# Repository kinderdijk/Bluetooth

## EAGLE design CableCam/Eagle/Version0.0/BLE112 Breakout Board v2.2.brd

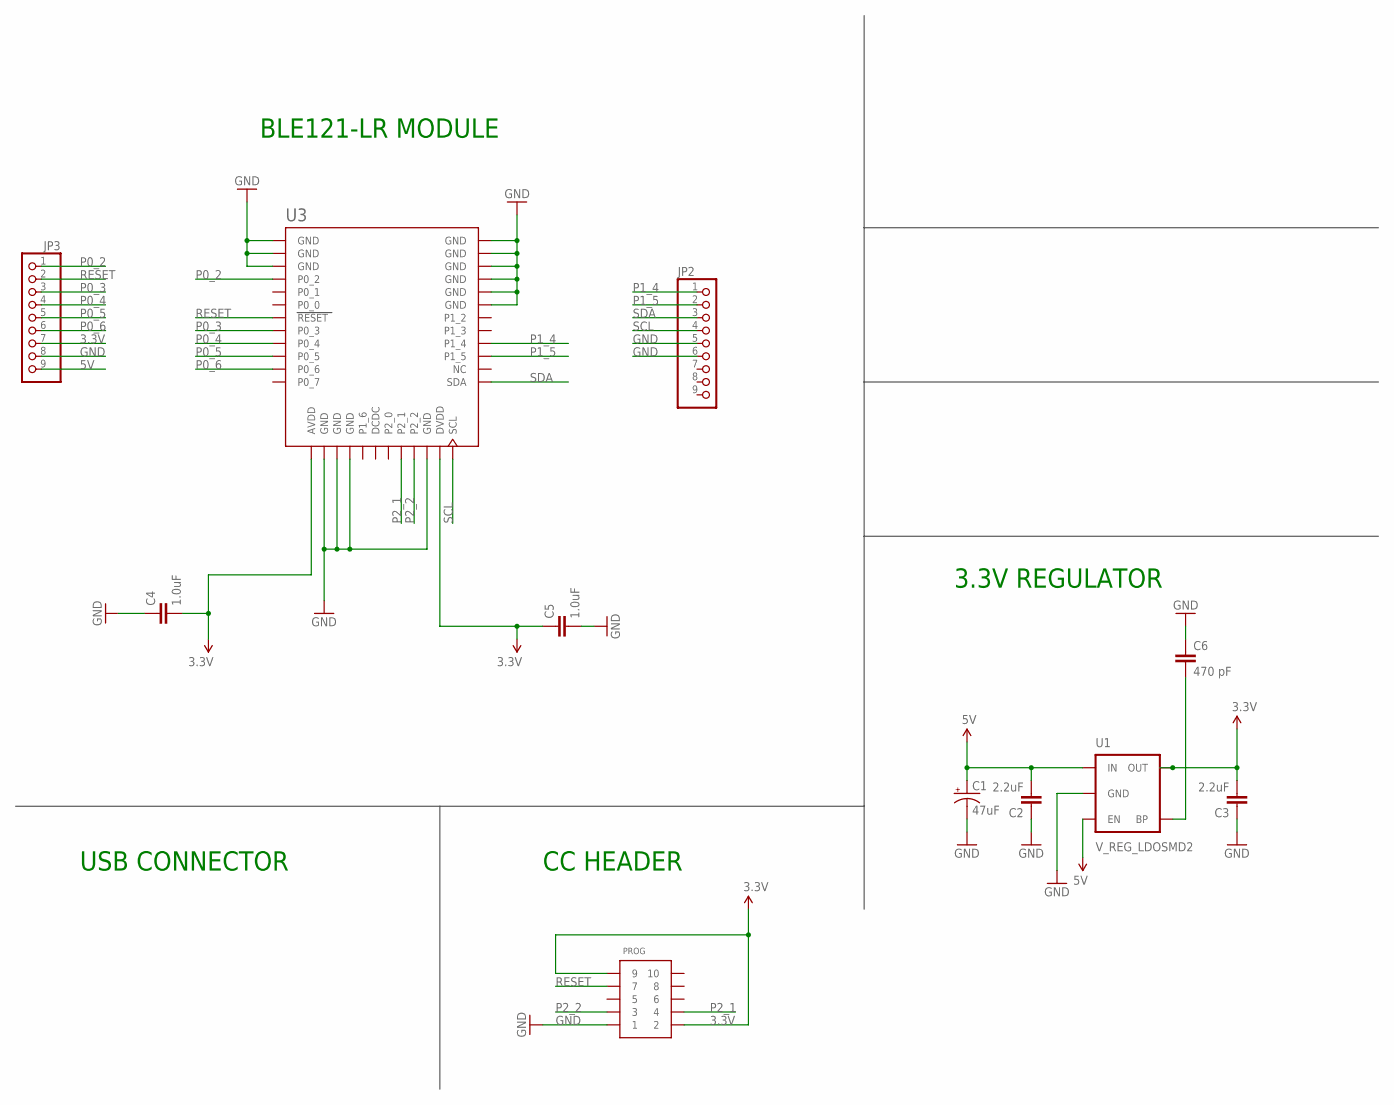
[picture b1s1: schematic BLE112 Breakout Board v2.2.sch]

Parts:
C1: 47uF; PANASONIC_D
C2, C3: 2.2uF; 0402-CAP
C4, C5: 1.0uF; 0402-CAP
C6: 470 pF; 0402-CAP
JP2, JP3: PINHD-1X9; 1X09-BIG
PROG: CONN_5-2-FTSH-V; FTSH-105-DV
U1: V_REG_LDOSMD2; SC70
U3: BLE121LR-VISUAL-A; BLE121LR-A

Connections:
3.3V: C3.2, C4.2, C5.1, JP3.7, PROG.2, PROG.9, U1.5 (OUT), U3.AVDD, U3.DVDD
5V: C1.+, C2.2, JP3.9, U1.1 (IN), U1.3 (EN)
GND: C1.-, C2.1, C3.1, C4.1, C5.2, C6.1, JP2.5, JP2.6, JP3.8, PROG.1, U1.2 (GND), U3.GND, U3.GND@2 (GND), U3.GND@3 (GND), U3.GND@4 (GND), U3.GND@5 (GND), U3.GND@6 (GND), U3.GND@7 (GND), U3.GND@8 (GND), U3.GND@9 (GND), U3.GND@10 (GND), U3.GND@11 (GND), U3.GND@12 (GND), U3.GND@13 (GND)
unnamed: C6.2, U1.4 (BP)
P0_2: JP3.1, U3.P0_2
P0_3: JP3.3, U3.P0_3
P0_4: JP3.4, U3.P0_4
P0_5: JP3.5, U3.P0_5
P0_6: JP3.6, U3.P0_6
P1_4: JP2.1, U3.P1_4
P1_5: JP2.2, U3.P1_5
P2_1: PROG.4, U3.P2_1
P2_2: PROG.3, U3.P2_2
RESET: JP3.2, PROG.7, U3.RESET
SCL: JP2.4, U3.SCL
SDA: JP2.3, U3.SDA

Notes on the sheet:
USB CONNECTOR
CC HEADER
3.3V REGULATOR
BLE121-LR MODULE

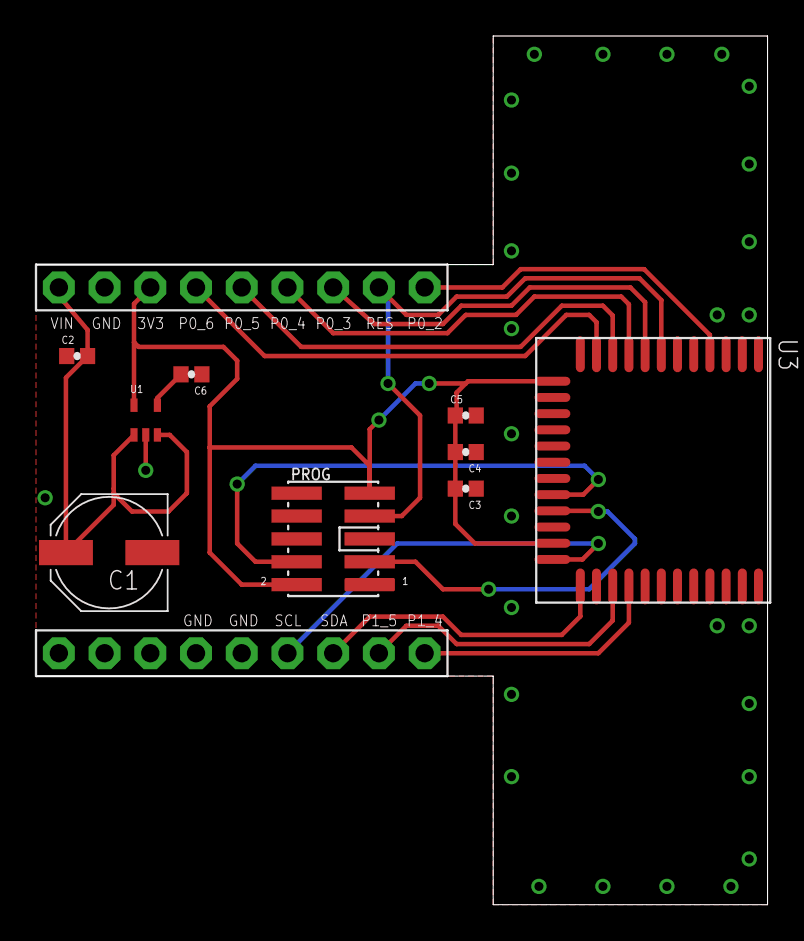
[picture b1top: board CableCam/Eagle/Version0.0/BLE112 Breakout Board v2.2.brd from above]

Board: 2 copper layers, 40.6 x 48.3 mm, 11 parts (0 on the bottom side), 16 nets.

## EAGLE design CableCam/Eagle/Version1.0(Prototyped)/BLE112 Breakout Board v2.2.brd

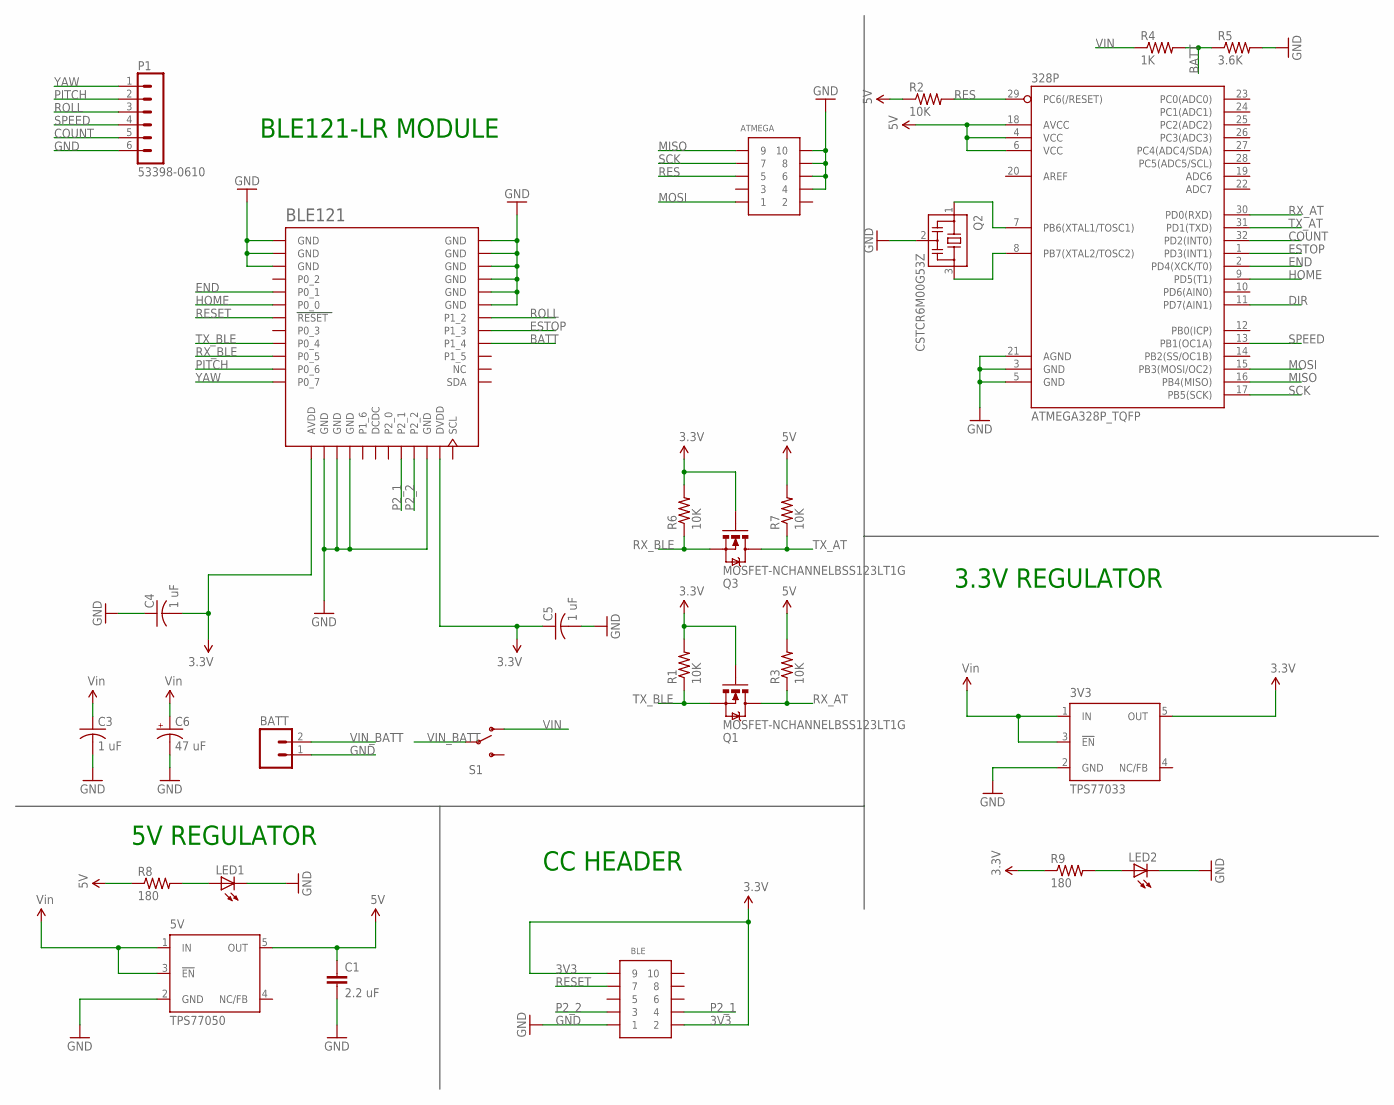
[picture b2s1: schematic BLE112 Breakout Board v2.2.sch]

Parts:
3V3: TPS77033; SOT23-DBV
5V: TPS77050; SOT23-DBV
328P: ATMEGA328P_TQFP; TQFP32-08
ATMEGA: CONN_5-2-FTSH-V; FTSH-105-DV
BATT: M02JST-PTH-2; JST-2-PTH
BLE: CONN_5-2-FTSH-V; FTSH-105-DV
BLE121: BLE121LR-VISUAL-A; BLE121LR-A
C1: 2.2 uF; 0603-CAP
C3, C4, C5: 1 uF; C0402
C6: 47 uF; PANASONIC_D
LED1, LED2: LEDSML0603; SML0603
P1: 53398-0610
Q1, Q3: MOSFET-NCHANNELBSS123LT1G; SOT23-3
Q2: CSTCR6M00G53Z; CSTCR6M
R1, R2, R3, R6, R7: 10K; R0402
R4: 1K; R0402
R5: 3.6K; R0402
R8, R9: 180; R0402
S1: SWITCH-SPDTSMD; AYZ0202

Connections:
3V3: 3V3.5 (OUT), BLE.2, BLE.9, BLE121.AVDD, BLE121.DVDD, C4.2, C5.1, Q1.1 (G), Q3.1 (G), R1.2, R6.2, R9.1
5V: 5V.5 (OUT), 328P.4 (VCC), 328P.6 (VCC), 328P.18 (AVCC), C1.1, R2.1, R3.2, R7.2, R8.1
BATT: BLE121.P1_4, R4.2, R5.1
COUNT: 328P.32 (PD2(INT0)), P1.5
DIR: 328P.11 (PD7(AIN1))
END: 328P.2 (PD4(XCK/T0)), BLE121.P0_1
ESTOP: 328P.1 (PD3(INT1)), BLE121.P1_3
GND: 3V3.2 (GND), 5V.2 (GND), 328P.3 (GND), 328P.5 (GND), 328P.21 (AGND), ATMEGA.4, ATMEGA.6, ATMEGA.8, ATMEGA.10, BATT.1, BLE.1, BLE121.GND, BLE121.GND@2 (GND), BLE121.GND@3 (GND), BLE121.GND@4 (GND), BLE121.GND@5 (GND), BLE121.GND@6 (GND), BLE121.GND@7 (GND), BLE121.GND@8 (GND), BLE121.GND@9 (GND), BLE121.GND@10 (GND), BLE121.GND@11 (GND), BLE121.GND@12 (GND), BLE121.GND@13 (GND), C1.2, C3.2, C4.1, C5.2, C6.-, LED1.C, LED2.C, P1.6, Q2.2, R5.2
HOME: 328P.9 (PD5(T1)), BLE121.P0_0
MISO: 328P.16 (PB4(MISO)), ATMEGA.9
MOSI: 328P.15 (PB3(MOSI/OC2)), ATMEGA.1
unnamed: 328P.8 (PB7(XTAL2/TOSC2)), Q2.3
unnamed: 328P.7 (PB6(XTAL1/TOSC1)), Q2.1
unnamed: LED1.A, R8.2
unnamed: LED2.A, R9.2
P2_1: BLE.4, BLE121.P2_1
P2_2: BLE.3, BLE121.P2_2
PITCH: BLE121.P0_6, P1.2
RES: 328P.29 (PC6(/RESET)), ATMEGA.5, R2.2
RESET: BLE.7, BLE121.RESET
ROLL: BLE121.P1_2, P1.3
RX_AT: 328P.30 (PD0(RXD)), Q1.3 (D), R3.1
RX_BLE: BLE121.P0_5, Q3.2 (S), R6.1
SCK: 328P.17 (PB5(SCK)), ATMEGA.7
SPEED: 328P.13 (PB1(OC1A)), P1.4
TX_AT: 328P.31 (PD1(TXD)), Q3.3 (D), R7.1
TX_BLE: BLE121.P0_4, Q1.2 (S), R1.1
VIN: 3V3.1 (IN), 3V3.3 (!EN), 5V.1 (IN), 5V.3 (!EN), C3.1, C6.+, R4.1, S1.1 (O)
VIN_BATT: BATT.2, S1.2
YAW: BLE121.P0_7, P1.1

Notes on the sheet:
5V REGULATOR
CC HEADER
3.3V REGULATOR
BLE121-LR MODULE

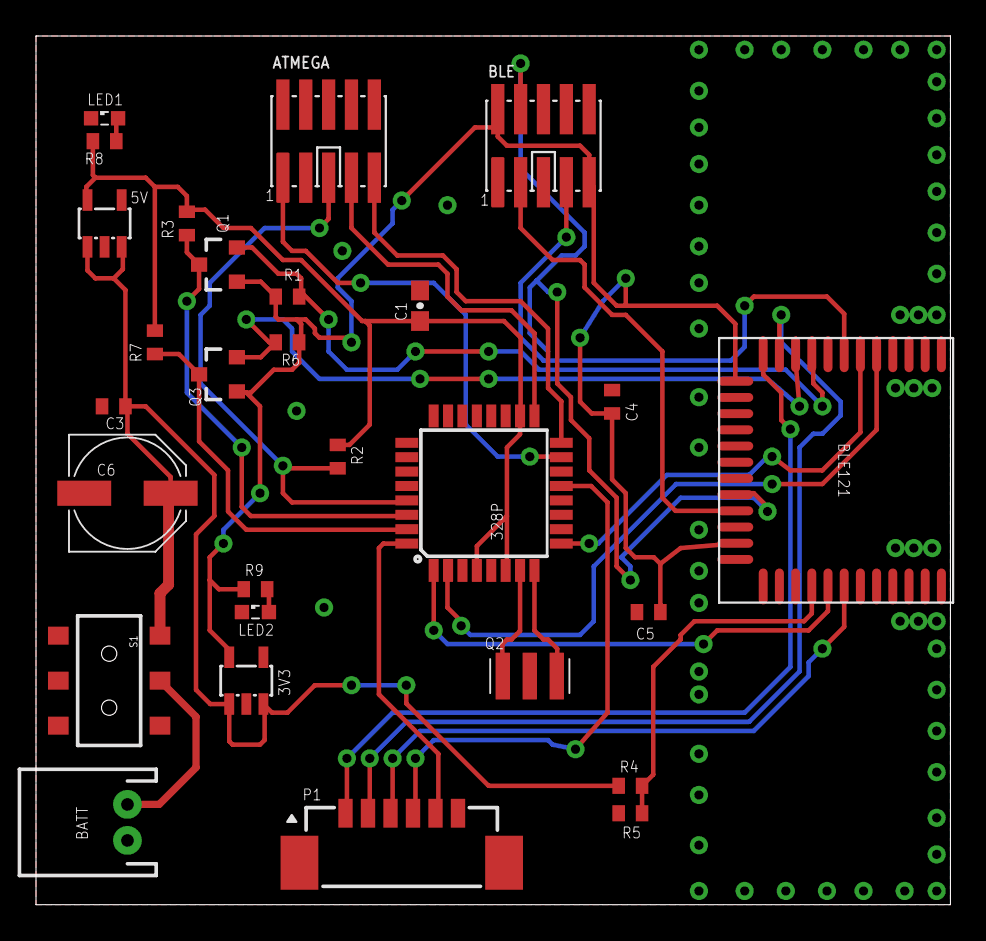
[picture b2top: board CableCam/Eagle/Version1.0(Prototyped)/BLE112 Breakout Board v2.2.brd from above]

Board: 2 copper layers, 50.8 x 48.3 mm, 28 parts (0 on the bottom side), 29 nets.

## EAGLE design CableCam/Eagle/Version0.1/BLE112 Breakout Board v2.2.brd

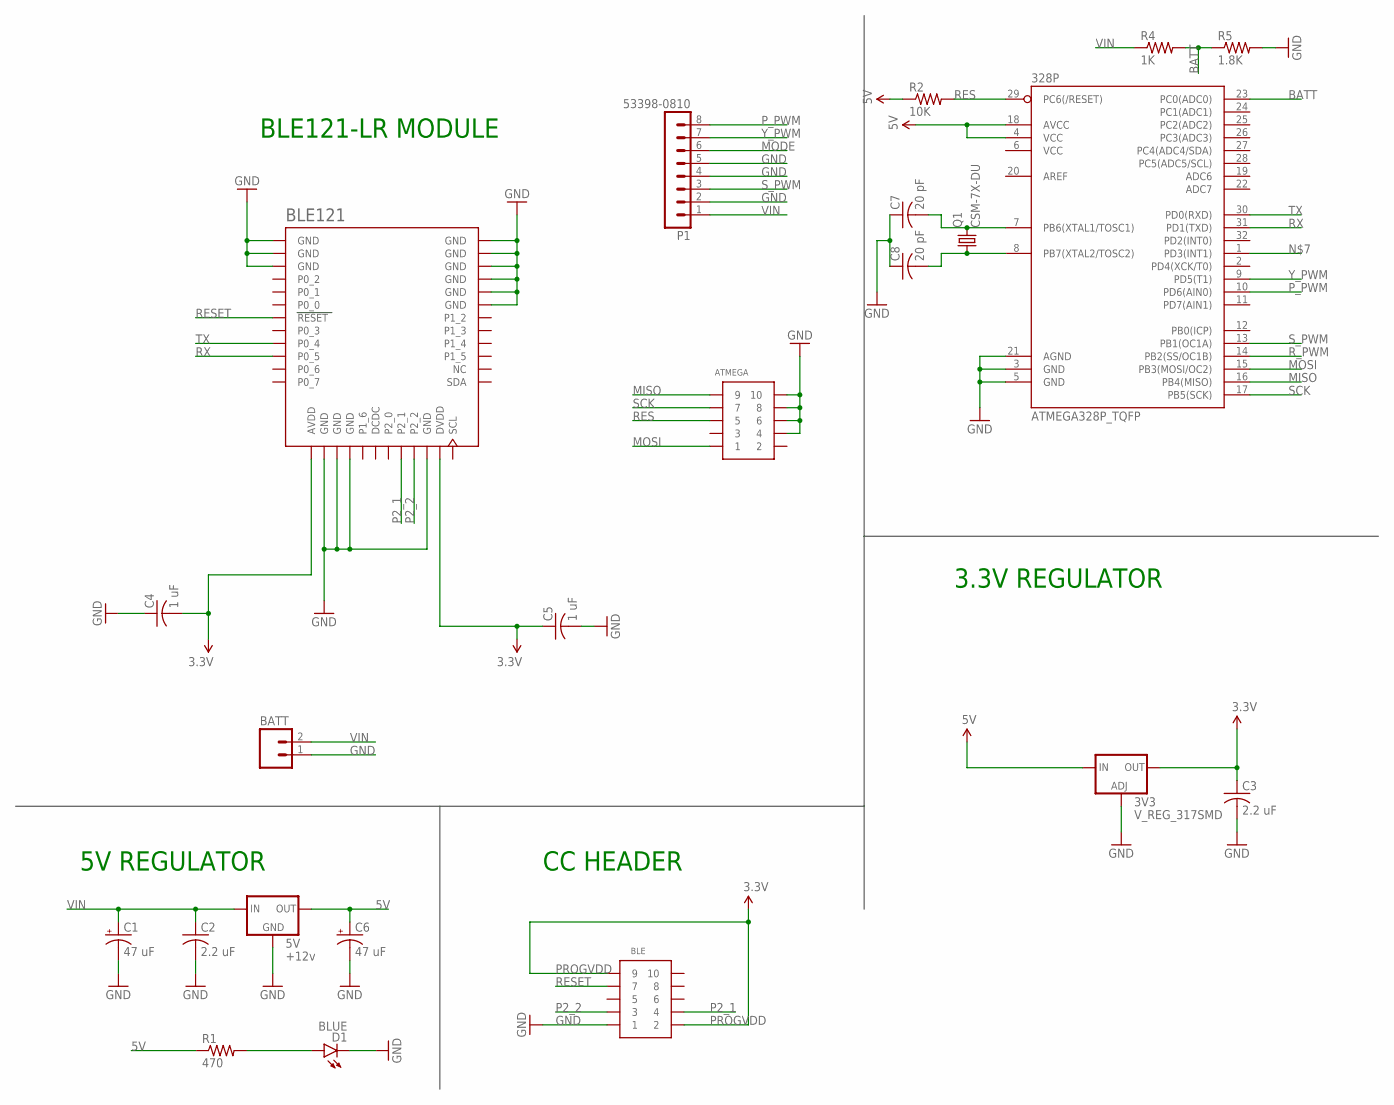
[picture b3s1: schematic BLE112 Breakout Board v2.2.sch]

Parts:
3V3: V_REG_317SMD; SOT223
5V: +12v; TO-252
328P: ATMEGA328P_TQFP; TQFP32-08
ATMEGA: CONN_5-2-FTSH-V; FTSH-105-DV
BATT: M02JST-PTH-2; JST-2-PTH
BLE: CONN_5-2-FTSH-V; FTSH-105-DV
BLE121: BLE121LR-VISUAL-A; BLE121LR-A
C1, C6: 47 uF; 153CLV-0405
C2, C3: 2.2 uF; C0402
C4, C5: 1 uF; C0402
C7, C8: 20 pF; C0402
D1: BLUE; LED-0603
P1: 53398-0810
Q1: CSM-7X-DU
R1: 470; R0402
R2: 10K; R0402
R4: 1K; R0402
R5: 1.8K; R0402

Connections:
5V: 3V3.3 (IN), 5V.2 (OUT), 328P.4 (VCC), 328P.18 (AVCC), C6.+, R1.1, R2.1
BATT: 328P.23 (PC0(ADC0)), R4.2, R5.1
GND: 3V3.1 (ADJ), 5V.3 (GND), 328P.3 (GND), 328P.5 (GND), 328P.21 (AGND), ATMEGA.4, ATMEGA.6, ATMEGA.8, ATMEGA.10, BATT.1, BLE.1, BLE121.GND, BLE121.GND@2 (GND), BLE121.GND@3 (GND), BLE121.GND@4 (GND), BLE121.GND@5 (GND), BLE121.GND@6 (GND), BLE121.GND@7 (GND), BLE121.GND@8 (GND), BLE121.GND@9 (GND), BLE121.GND@10 (GND), BLE121.GND@11 (GND), BLE121.GND@12 (GND), BLE121.GND@13 (GND), C1.-, C2.2, C3.2, C4.1, C5.2, C6.-, C7.1, C8.1, D1.C, P1.2, P1.4, P1.5, R5.2
MISO: 328P.16 (PB4(MISO)), ATMEGA.9
MODE: P1.6
MOSI: 328P.15 (PB3(MOSI/OC2)), ATMEGA.1
unnamed: D1.A, R1.2
unnamed: 328P.7 (PB6(XTAL1/TOSC1)), C7.2, Q1.2
unnamed: 328P.8 (PB7(XTAL2/TOSC2)), C8.2, Q1.1
P2_1: BLE.4, BLE121.P2_1
P2_2: BLE.3, BLE121.P2_2
PROGVDD: 3V3.2 (OUT), BLE.2, BLE.9, BLE121.AVDD, BLE121.DVDD, C3.1, C4.2, C5.1
P_PWM: 328P.10 (PD6(AIN0)), P1.8
RES: 328P.29 (PC6(/RESET)), ATMEGA.5, R2.2
RESET: BLE.7, BLE121.RESET
RX: 328P.31 (PD1(TXD)), BLE121.P0_5
R_PWM: 328P.14 (PB2(SS/OC1B))
SCK: 328P.17 (PB5(SCK)), ATMEGA.7
S_PWM: 328P.13 (PB1(OC1A)), P1.3
TX: 328P.30 (PD0(RXD)), BLE121.P0_4
VIN: 5V.1 (IN), BATT.2, C1.+, C2.1, P1.1, R4.1
Y_PWM: 328P.9 (PD5(T1)), P1.7

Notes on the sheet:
5V REGULATOR
CC HEADER
3.3V REGULATOR
BLE121-LR MODULE

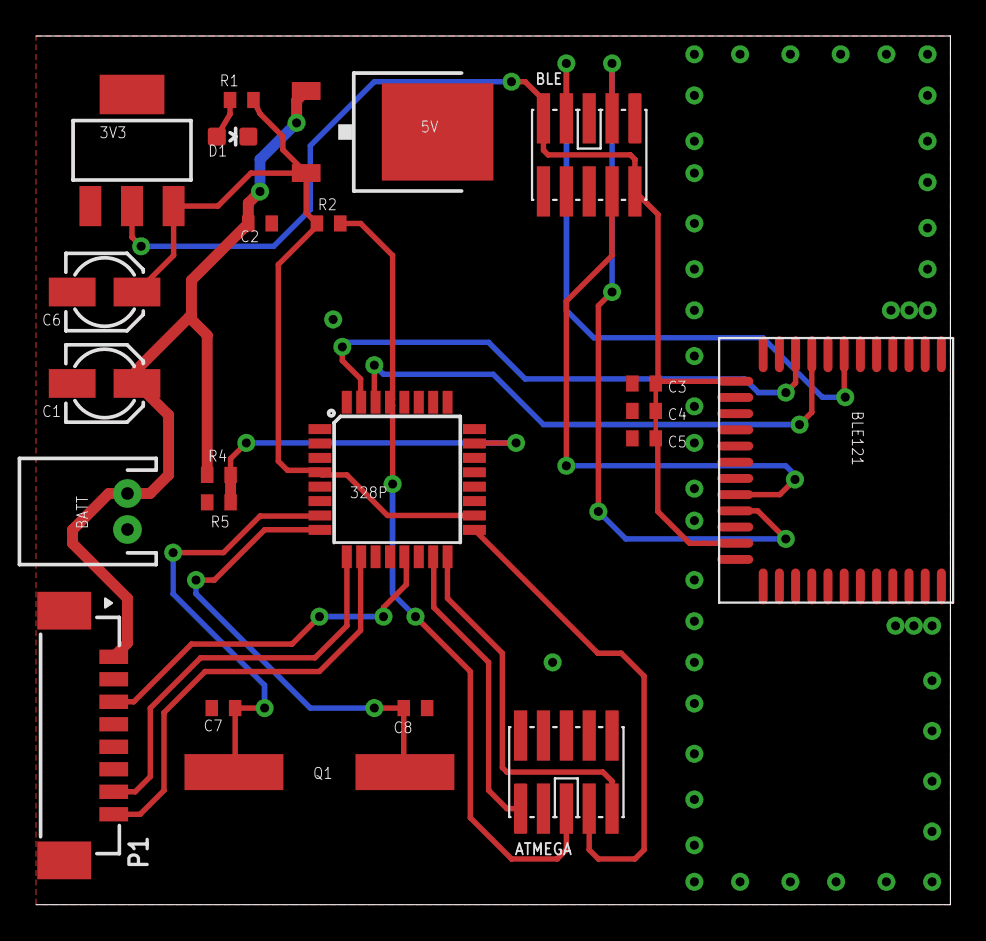
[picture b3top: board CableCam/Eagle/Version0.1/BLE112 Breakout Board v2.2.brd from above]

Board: 2 copper layers, 50.8 x 48.3 mm, 22 parts (0 on the bottom side), 20 nets.

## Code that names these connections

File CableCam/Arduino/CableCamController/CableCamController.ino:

/*
 *
 * CableCamController
 *
 * This program is meant to handle the serial commuication of the BlueGiga 
 * bluetooth module. It will receive instructions from the module, process
 * data, perform the controls and calculations and return information and 
 * data to the module to be send back to the phone.
 *
 */
 
#define _BV(bit) (1<<(bit));
 
#include <avr/io.h>
#include <avr/interrupt.h>
#include <avr/wdt.h>

// Create a software serial port for ble input.
//SoftwareSerial cable_serial(5,6);
#define battery_pin A0
#define speed_pin 9
#define yaw_pin 5
#define roll_pin 10
#define pitch_pin 6

int previous_battery_value;
int battery;
int battery_count;
double battery_ave;
volatile int timer_battery_count;
byte send_battery_value;

byte input_type;
byte input_value;

byte roll_value;
byte yaw_value;
byte pitch_value;

/*
 *
 *  Type code for serial communication.
 *  Gimbal yaw/pitch    1
 *  Gimbal roll         3
 *  speed               2
 *  battery             4
 *  end                 5
 *
 */
const int GIMBAL_OTHER_TYPE = 1;
const int GIMBAL_ROLL_TYPE = 3;
const int SPEED_TYPE = 2;
const int BATTERY_TYPE = 4;
const int END_SET_TYPE = 5;
const int BATTERY_AVERAGE = 16;
const int DISCONNECT = 255;

enum States
{
  STATE_INIT,
  STATE_WAIT_FOR_COMMAND,
  STATE_UART_READ,
  STATE_UPDATE_PWM,
  STATE_UPDATE_BATTERY
} state;

class SpeedMeasure
{
  int endingRotation;
  long previousMils;
  long timeInterval;
  long count;
  
  public:
  SpeedMeasure()
  {
    count = 0;
    previousMils = 0;
  }
  
  void resetCount()
  {
    count = 0;
  }
  
  void setEnding()
  {
    endingRotation = count;
  }
  
  void update(long currentMils)
  {
    // Depends on direction!!!
    count++;
    timeInterval = currentMils - previousMils;
    previousMils = currentMils;
  }
};

SpeedMeasure speedMeasure;
 
void setup()
{
  //////////////////////////////////////////////////////
  // ATMEGA 328 without the arduino board is clocked at
  // 8MHz, not 16MHz. But the bootloader requires a 
  // requires a crystal for timing precies enough for
  // serial communication.
  //////////////////////////////////////////////////////
  
  // Set up the pwm code.
  pinMode(speed_pin, OUTPUT);
  pinMode(roll_pin, OUTPUT);
  pinMode(yaw_pin, OUTPUT);
  pinMode(pitch_pin, OUTPUT);

  //////////////////////////////////////////////////////
  //  Timer 1 Setup
  //////////////////////////////////////////////////////
  // Set fast pwm mode, with inverted mode. (pulse high)
  TCCR1A = 0x00;
  TCCR1A = _BV(WGM11) | _BV(COM1A1) | _BV(COM1B1);
  TCCR1B = 0x00;
  TCCR1B = _BV(WGM13) | _BV(WGM12) | _BV(CS11);
  
  // Set the TOP value. 16MHz/8 = 2MHz. 2HMz/(0x9C3F+1) = 50Hz.
  ICR1 = 0x9C3F;
  
  // This should equate to a 50% duty cycle.
  OCR1A = 0x4E1F;   // Pin9
  OCR1B = 0x4E1F;   // Pin10

  //////////////////////////////////////////////////////
  //  Timer 0 Setup
  //////////////////////////////////////////////////////
  // Setup pwm for Timer0 for the gimbal measure.
  TCCR0A = 0x00;
  TCCR0A = _BV(COM0A1) | _BV(COM0B1) | _BV(WGM00) | _BV(WGM01);
  TCCR0B = 0x00;
  TCCR0B = _BV(CS00) | _BV(CS02);
  cli();
  TIMSK0 = 0x00;
  TIMSK0 = _BV(OCIE0A);
  sei();

  // Set TOP value. 16MHz/1024 = 15.625KHz. 15.625KHz/256 = 61Hz (8bit timer)
  OCR0A = 16;     // Pin6

  // 50% duty cycle.
  OCR0B = 16;     // Pin5
  
  Serial.begin(9600);
  
  state = STATE_WAIT_FOR_COMMAND;
  previous_battery_value = 0;
  battery_count = 0;
  timer_battery_count = 0;

  Serial.flush();
}

void loop()
{
  
  switch (state)
  {   
    case STATE_WAIT_FOR_COMMAND:
      if (Serial.available() >= 1)
      {
        state = STATE_UART_READ;
        break;
      }

      battery_ave += analogRead(battery_pin);
      battery_count += 1;
      if (timer_battery_count >= 610)
      {
        timer_battery_count = 0;
        state = STATE_UPDATE_BATTERY;
        break;
      }
      
      break;
      
    case STATE_UPDATE_BATTERY:
    {
      // The difference between full battery and empty battery is roughly 256 points.
      // Just send that value through and let xcode deal with the percentage.
      int diff_value = 1023 - (battery_ave/battery_count);
//      int diff_value = 1023 - previous_battery_value;
      send_battery_value = 256-diff_value;
//      Serial.println(send_battery_value, HEX);

      
      Serial.write(BATTERY_TYPE);
      Serial.write(send_battery_value);

      battery_ave = 0;
      battery_count = 0;
      state = STATE_WAIT_FOR_COMMAND;
      break;
    }
      
    case STATE_UART_READ:
      input_type = Serial.read();
      if (input_type == GIMBAL_OTHER_TYPE)
      { 
        pitch_value = Serial.read();
        delay(10);
        yaw_value = Serial.read();

        int yaw_pwm = ((2*yaw_value) >> 4) + 16;
        int pitch_pwm = ((2*pitch_value) >> 4) + 16;
        OCR0A = yaw_pwm;          // Pin6 || 12
        OCR0B = pitch_pwm;        // Pin5 || 11
      }
      else if (input_type == GIMBAL_ROLL_TYPE)
      {
        // Roll is controlled by a slider, so it will have a 200 top value.
        roll_value = Serial.read();
        OCR1B = 10*roll_value + 2000;   // Pin10 || 16
      }
      else if (input_type == SPEED_TYPE)
      {
        input_value = Serial.read();
        OCR1A = 10*input_value + 2000;  // Pin9 || 15
      }
      else if (input_type == END_SET_TYPE)
      {
        // This will have to take into account the direction of the motor.
        // Can be determined from pwm value.
        speedMeasure.setEnding();
      }
      else if (input_type == DISCONNECT)
      {
        // Set all the pwm pins to a 50% duty cycle.
        OCR1A = 0x4E1F;   // Pin9
        OCR1B = 0x4E1F;   // Pin10 
        OCR0B = 16;     // Pin5
      }
      
      state = STATE_WAIT_FOR_COMMAND;
      break;
  }
}

ISR(TIMER0_COMPA_vect)
{
  timer_battery_count++;
}

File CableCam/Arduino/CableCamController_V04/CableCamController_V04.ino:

//#define _BV(bit) (1<<(bit));

#include <avr/interrupt.h>
#include <avr/io.h>
#include "SoftwareSerial.h"
#include <math.h>

#define E 2.718
#define constant -0.14

int countPin      = 2;     //PD2, Bread 4, Proto 32
int stopPin       = 3;     //PD3, Bread 5, Proto 1
int endSetPin     = 4;     //PD4, Bread 6, Proto 2
int homeSetPin    = 5;     //PD5, Bread 11, Proto 9
int speedPin      = 9;     //PB1, Bread 15, Proto 13

int serialPin = 13;

int volatile currentPosition = 0;
int volatile camDirection = 1;
int currentCount = 0;

int requestDirection = 1;
int requestSpeed = 0;

bool volatile isStopped = false;

int homePoint = 0xFFFF;
int endPoint = 0xFFFF;
int homeSetState = 0x0;
int endSetState = 0x0;
bool isHomeSet = false;
bool isEndSet = false;

int maxPwmValue = 0x0FA0;
int minPwmValue = 0x07D0;
int neutralPwmValue = 0x0BB8;

int pwmSpread = (maxPwmValue-minPwmValue)/2;
int pwmInterval = pwmSpread/7;

int endRemaining = 0x7FFF;
int homeRemaining = 0x7FFF;

int slowPoint = 100;
int setCount = 0x7FFF;

byte input_value;

//SoftwareSerial softSerial(A0, serialPin);

enum States
{
  STATE_WAIT_FOR_COMMAND,
  STATE_SERIAL_READ,
  STATE_ESTOP,
  STATE_SET_HOME,
  STATE_SET_END,
  STATE_SET_END_SPEED_LIMIT,
  STATE_SET_HOME_SPEED_LIMIT
} state;

void setup() {
  // put your setup code here, to run once:
  pinMode(speedPin, OUTPUT);
  pinMode(countPin, INPUT);
  pinMode(stopPin, INPUT);

  // Set pin PD4 and PD5 to inputs. Doing it this way is an attempt to reduce time.
  DDRD &= 0b11001111;
  
  //////////////////////////////////////////////////////
  //  Timer 1 Setup
  //////////////////////////////////////////////////////
  // Set fast pwm mode, with inverted mode. (pulse high)
  TCCR1A = 0x00;
  TCCR1A = _BV(WGM11) | _BV(COM1A1) | _BV(COM1B1);
  TCCR1B = 0x00;
  TCCR1B = _BV(WGM13) | _BV(WGM12) | _BV(CS11);
  
  // Set the TOP value. 16MHz/8 = 2MHz. 2HMz/(0x9C3F+1) = 50Hz.
  ICR1 = 0x9C3F;
  
  // Working duty cycle is between 5-10%. (2000-4000)
  OCR1A = neutralPwmValue;   // Pin9 (A)

  // Begin the serial connection.
  Serial.begin(57600);
  Serial.flush();

//  softSerial.begin(115200);

  attachInterrupt(0, count, RISING);
  attachInterrupt(1, eStop, RISING);

  interrupts();

  state = STATE_WAIT_FOR_COMMAND;
}

void loop() {
  cli();
  currentCount = currentPosition;
  sei();

  // If the home and end points are set, determine how far from them we are.
  if (isEndSet) endRemaining = endPoint-currentCount;
  if (isHomeSet) homeRemaining = currentCount-homePoint;

  // If the cable cam is supposed to be stopped but still gets counts those are not counted.
  if (OCR1A > 3000) camDirection = 1;
  else if (OCR1A < 3000) camDirection = -1;
  
  switch (state)
  {
    
    case STATE_WAIT_FOR_COMMAND:
      // Check if the estop button has been pressed.
      if (isStopped) 
      {
        state = STATE_ESTOP;
        break;
      }

      // Check if the state if the home set button has changed.
      if ((PIND & (1<<PD5)) != homeSetState)
      {
        homeSetState = (PIND & (1<<PD5));
        state = STATE_SET_HOME;
        break;
      }

      // Check if the state of the end set button has changed.
      if ((PIND & (1<<PD4)) != endSetState)
      {
        endSetState = (PIND & (1<<PD4));
        state = STATE_SET_END;
        break;
      }
      
      // If there is data available on the serial port read it.
      if (Serial.available() >= 1)
      {
        state = STATE_SERIAL_READ;
        break;
      }


      if (isEndSet && endRemaining < slowPoint && currentCount != setCount)
      {
        state = STATE_SET_END_SPEED_LIMIT;
        break;
      }

      // Check how close we are to the home point.
      if (isHomeSet && homeRemaining < slowPoint && currentCount != setCount)
      {
        state = STATE_SET_HOME_SPEED_LIMIT;
        break;
      }
      
      break;

    case STATE_SERIAL_READ:
      input_value = Serial.read();
      
      // Make sure these values don't violate the speed limits.
      requestSpeed = 10*input_value + 2000;
      if (requestSpeed == 3000)
      {
        requestDirection = 0;
      }
      else
      {
        requestDirection = requestSpeed > 3000 ? 1 : -1;
      }

      if (requestDirection > 0)
      {
        if (isEndSet && endRemaining < slowPoint)
        {
          setPwmOverrideSpeed(endRemaining);
          state = STATE_WAIT_FOR_COMMAND;
          break;
        }
      }
      else if (requestDirection < 0)
      {
        if (isHomeSet && homeRemaining < slowPoint)
        {
          setPwmOverrideSpeed(homeRemaining);
          state = STATE_WAIT_FOR_COMMAND;
          break;
        }
      }

      OCR1A = requestSpeed;

      state = STATE_WAIT_FOR_COMMAND;
      break;

    case STATE_ESTOP:
      // Stay in this state until the button is released.
      if (isStopped) OCR1A = 0x0BB8; // Neutral duty cycle (3000)

      if (PIND & (1<<PD3))
      {
        isStopped = false;
        state = STATE_WAIT_FOR_COMMAND;
        break;
      }

      break;

    case STATE_SET_HOME:
      if (PIND & (1<<PD5))
      {
        isHomeSet = true;
        homePoint = currentCount;
        softSerial.print(currentCount);
      }
      else
      {
        isHomeSet = false;
        homePoint = 0;
        homeRemaining = 0x7FFF;
      }

      state = STATE_WAIT_FOR_COMMAND;
      break;

    case STATE_SET_END:
      if (PIND & (1<<PD4))
      {
        isEndSet = true;
        endPoint = currentCount;
      }
      else
      {
        isEndSet = false;
        endPoint = 0;
        endRemaining = 0x7FFF;
      }

      state = STATE_WAIT_FOR_COMMAND;
      break;

    case STATE_SET_END_SPEED_LIMIT:
      
      if (camDirection > 0)
      {
        setPwmOverrideSpeed(endRemaining);
      }

      state = STATE_WAIT_FOR_COMMAND;
      break;

    case STATE_SET_HOME_SPEED_LIMIT:
      if (camDirection < 0)
      {
        setPwmOverrideSpeed(homeRemaining);
      }

      state = STATE_WAIT_FOR_COMMAND;
      break;
  }
}

void setPwmOverrideSpeed(int proximity)
{
  setCount = currentCount;

  if (proximity > 20)
  {
    double initialOffset = 2*proximity;
    int pwmOffset = floor(initialOffset);
      
    if (camDirection > 0)
    {
      int pwmLimit = neutralPwmValue + pwmOffset;
      if (pwmLimit < OCR1A)
      {
        OCR1A = pwmLimit;
      }
    }
    else if (camDirection < 0)
    {
      int pwmLimit = neutralPwmValue - pwmOffset;
      if (pwmLimit > OCR1A)
      {
        OCR1A = pwmLimit;
      }
    }
  }
  else
  {
    if (proximity == 0)
    {
      OCR1A = neutralPwmValue;
    }
    else if (proximity > 0)
    {
      if (camDirection > 0)
      {
        int pwmLimit = neutralPwmValue + 40;
        if (pwmLimit < OCR1A)
        {
          OCR1A = pwmLimit;
        }
      }
      else if (camDirection < 0)
      {
        int pwmLimit = neutralPwmValue - 40;
        if (pwmLimit > OCR1A)
        {
          OCR1A = pwmLimit;
        }
      }
    }
  }
}

void count()
{
  currentPosition += camDirection;
//  softSerial.print(currentPosition);
}

void eStop()
{
  isStopped = true;
}

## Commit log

2016-11-01 Initially added all the files stored in the folder.

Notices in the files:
parts and their libraries:
SparkFun-Capacitors: Licensing: Creative Commons ShareAlike 4.0 International - https://creativecommons.org/licenses/by-sa/4.0
SparkFun: Licensing: CC v3.0 Share-Alike You are welcome to use this library for commercial purposes.
con-molex-picoblade: Copyright (C) 2010, Bob Starr
